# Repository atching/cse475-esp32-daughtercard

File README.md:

Example KiCad Project for CSE/EE 475 Embedded Systems Capstone

This is an example KiCad pcb project that is a daughtercard for a SparkFun ESP32 Thing Plus. It shows how you would make a pcb that can plug into that Sparkfun board and include an accelerometer on it.

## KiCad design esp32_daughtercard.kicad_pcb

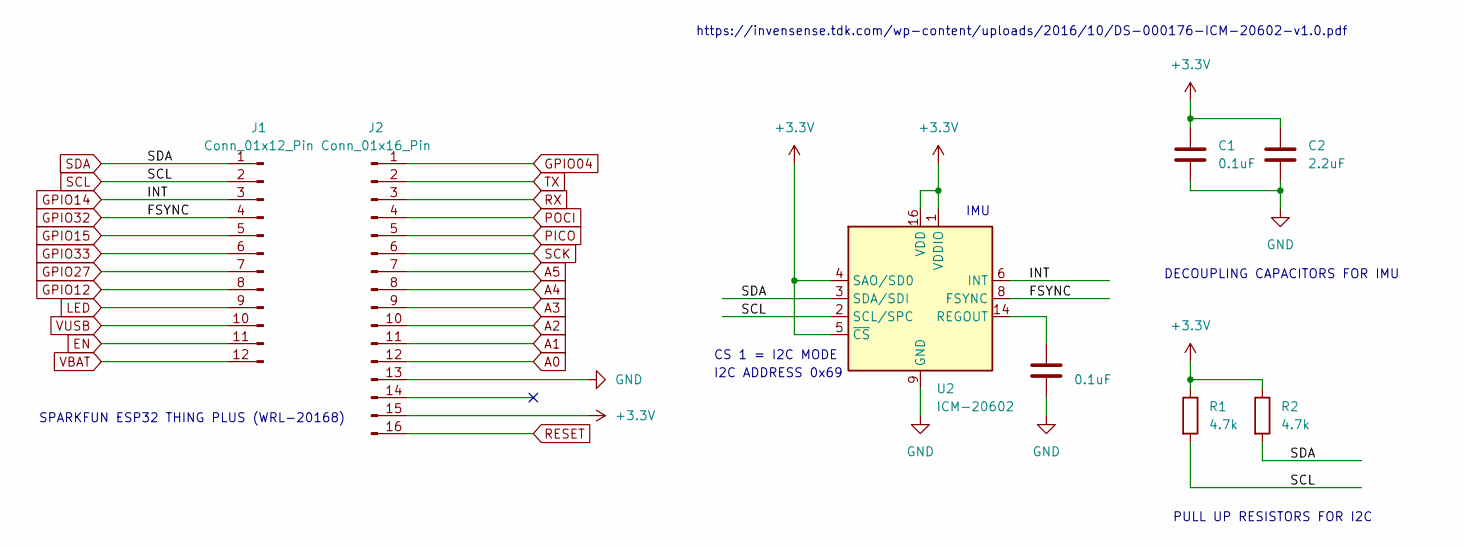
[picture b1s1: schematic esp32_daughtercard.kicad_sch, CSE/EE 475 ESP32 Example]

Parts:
C1, C3: 0.1uF; C_0805_2012Metric
C2: 2.2uF; C_0805_2012Metric
J1: Conn_01x12_Pin; PinHeader_1x12_P2.54mm_Vertical
J2: Conn_01x16_Pin; PinHeader_1x16_P2.54mm_Vertical
R1, R2: 4.7k; R_0805_2012Metric
U2: ICM-20602; LGA-16_3x3mm_P0.5mm_LayoutBorder3x5y

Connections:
+3.3V: C1.1, C2.1, J2.15, R1.1, R2.1, U2.1 (VDDIO), U2.4 (SAO/SD0), U2.5 (~CS), U2.16 (VDD)
A0: J2.12
A1: J2.11
A2: J2.10
A3: J2.9
A4: J2.8
A5: J2.7
EN: J1.11
GND: C1.2, C2.2, C3.2, J2.13, U2.9 (GND), U2.10 (GND), U2.11 (GND), U2.12 (GND), U2.13 (GND), U2.15 (GND)
GPIO04: J2.1
GPIO12: J1.8
GPIO14: J1.3, U2.6 (INT)
GPIO15: J1.5
GPIO27: J1.7
GPIO32: J1.4, U2.8 (FSYNC)
GPIO33: J1.6
LED: J1.9
unnamed: C3.1, U2.14 (REGOUT)
PICO: J2.5
POCI: J2.4
RESET: J2.16
RX: J2.3
SCK: J2.6
SCL: J1.2, R1.2, U2.2 (SCL/SPC)
SDA: J1.1, R2.2, U2.3 (SDA/SDI)
TX: J2.2
VBAT: J1.12
VUSB: J1.10

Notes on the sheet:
I2C ADDRESS 0x69
PULL UP RESISTORS FOR I2C
CS 1 = I2C MODE
IMU
https://invensense.tdk.com/wp-content/uploads/2016/10/DS-000176-ICM-20602-v1.0.pdf
SPARKFUN ESP32 THING PLUS (WRL-20168)
DECOUPLING CAPACITORS FOR IMU

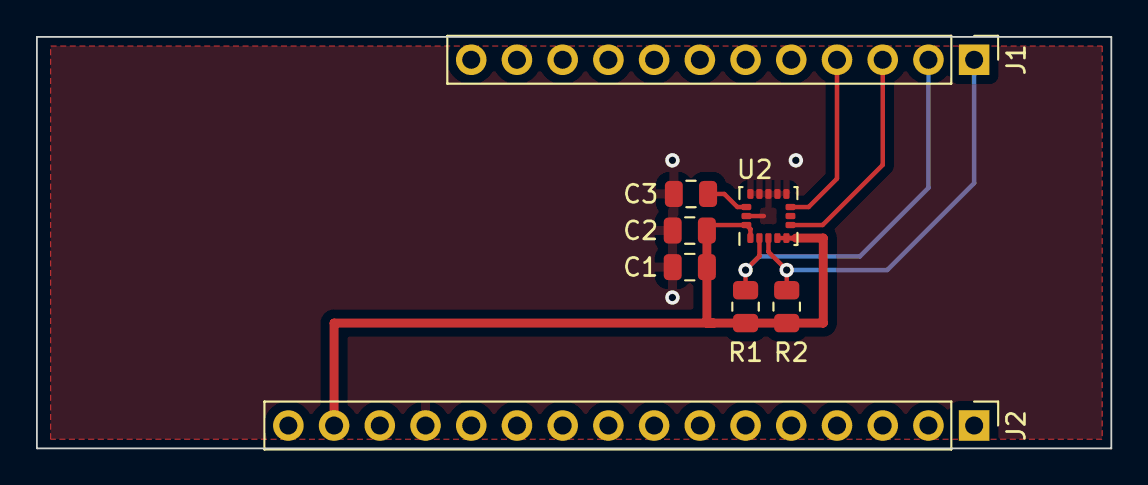
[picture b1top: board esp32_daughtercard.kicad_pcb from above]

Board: 2 copper layers, 59.7 x 22.9 mm, 8 parts (0 on the bottom side), 7 nets.
